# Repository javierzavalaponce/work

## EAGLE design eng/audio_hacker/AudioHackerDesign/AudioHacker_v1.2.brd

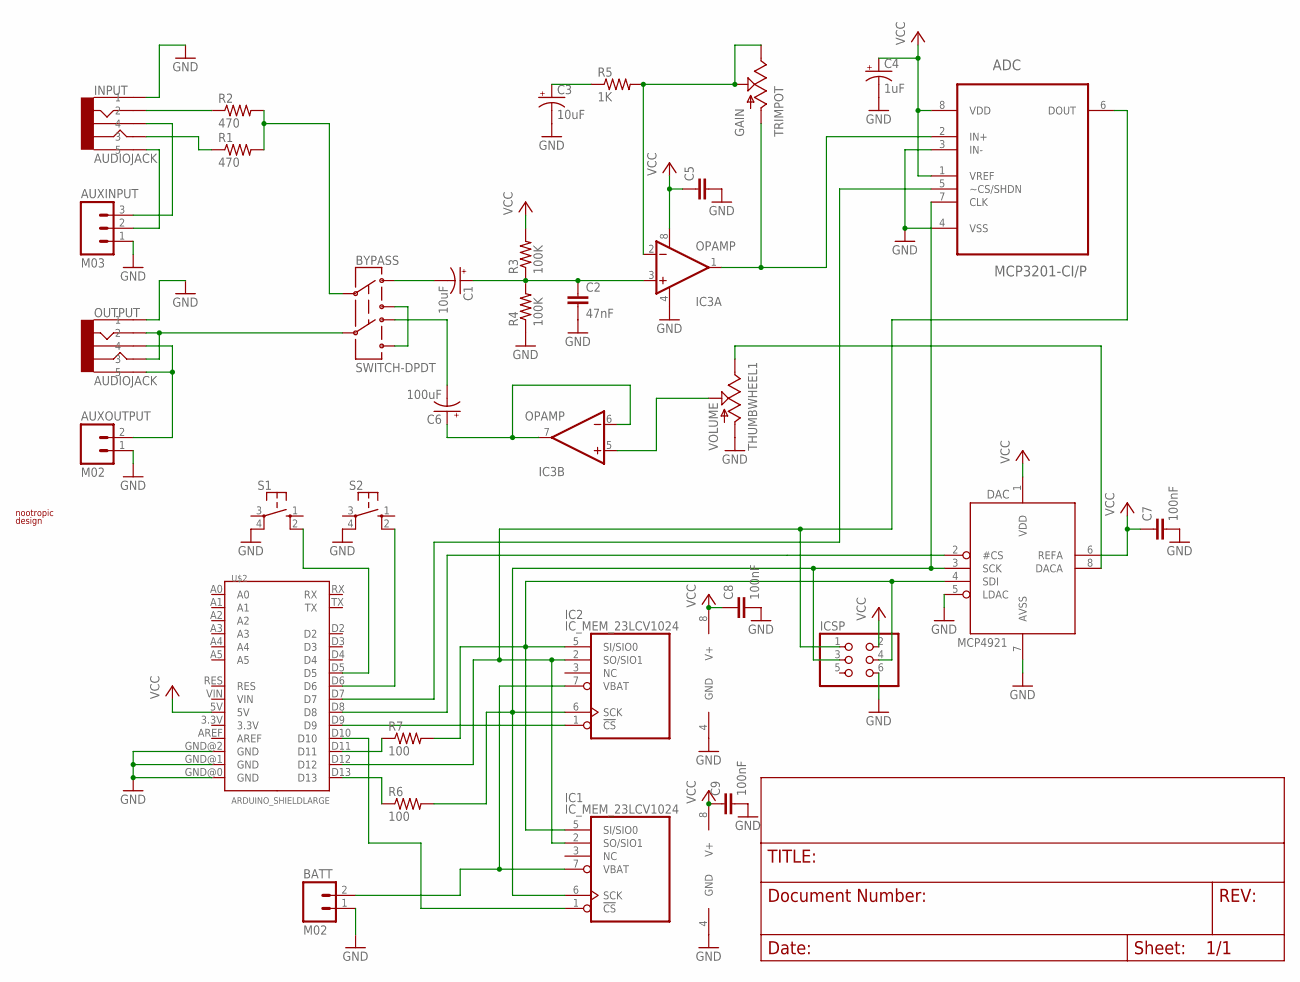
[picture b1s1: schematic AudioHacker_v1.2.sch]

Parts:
ADC: MCP3201-CI/P; DIL08
AUXINPUT: M03; 1X03
AUXOUTPUT: M02; 1X02
BATT: M02; 1X02
BYPASS: SWITCH-DPDT; OS
C1, C3: 10uF; E2.5-5
C2: 47nF; CAP-CERAMIC
C4: 1uF; E2.5-5
C5: CAPSMALL; CAP-CERAMIC-SMALL
C6: 100uF; E2.5-6
C7, C8, C9: 100nF; CAP-CERAMIC-SMALL
DAC: MCP4921; DIL08
GAIN: TRIMPOT; TRIM_POT
IC1, IC2: IC_MEM_23LCV1024; DIL08
IC3: OPAMP; DIL08
ICSP: PINHD-2X3; 2X03
INPUT: AUDIOJACK
OUTPUT: AUDIOJACK
R1, R2: 470; 0207/10
R3, R4: 100K; 0207/10
R5: 1K; 0207/10
R6, R7: 100; 0207/10
S1, S2: SWITCH-TACTSWITCH-TACT-B; SWITCH-TACT-B
U$2: ARDUINO_SHIELDLARGE; DUEMILANOVE_SHIELD_LARGE
U$3: LOGO; LOGO_SMALL
VOLUME: THUMBWHEEL1

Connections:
AMP_OUT: C6.+, IC3.6 (-IN), IC3.7 (OUT)
DAC_OUT: DAC.8 (DACA), VOLUME.P$3 (3)
DAC_OUT2: IC3.5 (+IN), VOLUME.P$2 (2)
GND: ADC.3 (IN-), ADC.4 (VSS), AUXINPUT.1 (2), AUXOUTPUT.1, BATT.1, C2.2, C3.-, C4.-, C5.2, C7.2, C8.2, C9.2, DAC.5 (LDAC), DAC.7 (AVSS), IC1.4 (GND), IC2.4 (GND), IC3.4 (V-), ICSP.6, INPUT.1, OUTPUT.1, R4.1, S1.4 (P1), S2.4 (P1), U$2.GND@0 (GND), U$2.GND@1 (GND), U$2.GND@2 (GND), VOLUME.P$1 (1)
INPUT: BYPASS.2, R1.2, R2.2
MISO: ADC.6 (DOUT), IC1.2 (SO/SIO1), IC2.2 (SO/SIO1), ICSP.1, U$2.D12
MOSI: DAC.4 (SDI), IC1.5 (SI/SIO0), IC2.5 (SI/SIO0), ICSP.4, R7.2
MOSIPIN: R7.1, U$2.D11
unnamed: AUXINPUT.3 (4), INPUT.4
unnamed: AUXINPUT.2 (3), INPUT.5
unnamed: AUXOUTPUT.2, OUTPUT.4, OUTPUT.5
unnamed: BYPASS.3, BYPASS.6
unnamed: INPUT.2, R2.1
unnamed: INPUT.3, R1.1
unnamed: GAIN.2, GAIN.3, IC3.2 (-IN), R5.2
unnamed: ADC.2 (IN+), GAIN.1, IC3.1 (OUT)
unnamed: C3.+, R5.1
unnamed: BYPASS.1, C1.-
unnamed: C1.+, C2.1, IC3.3 (+IN), R3.1, R4.2
unnamed: BYPASS.4, C6.-
unnamed: R6.1, U$2.D13
unnamed: ADC.5 (~CS/SHDN), U$2.D7
unnamed: DAC.2 (#CS), U$2.D8
unnamed: S2.2 (S1), U$2.D6
unnamed: IC1.1 (!CS), U$2.D10
unnamed: IC2.1 (!CS), U$2.D9
unnamed: S1.2 (S1), U$2.D5
OUTPUT: BYPASS.5, OUTPUT.2, OUTPUT.3
SCK: ADC.7 (CLK), DAC.3 (SCK), IC1.6 (SCK), IC2.6 (SCK), ICSP.3, R6.2
VBAT: BATT.2, IC1.7 (VBAT), IC2.7 (VBAT)
VCC: ADC.1 (VREF), ADC.8 (VDD), C4.+, C5.1, C7.1, C8.1, C9.1, DAC.1 (VDD), DAC.6 (REFA), IC1.8 (V+), IC2.8 (V+), IC3.8 (V+), ICSP.2, R3.2, U$2.5V

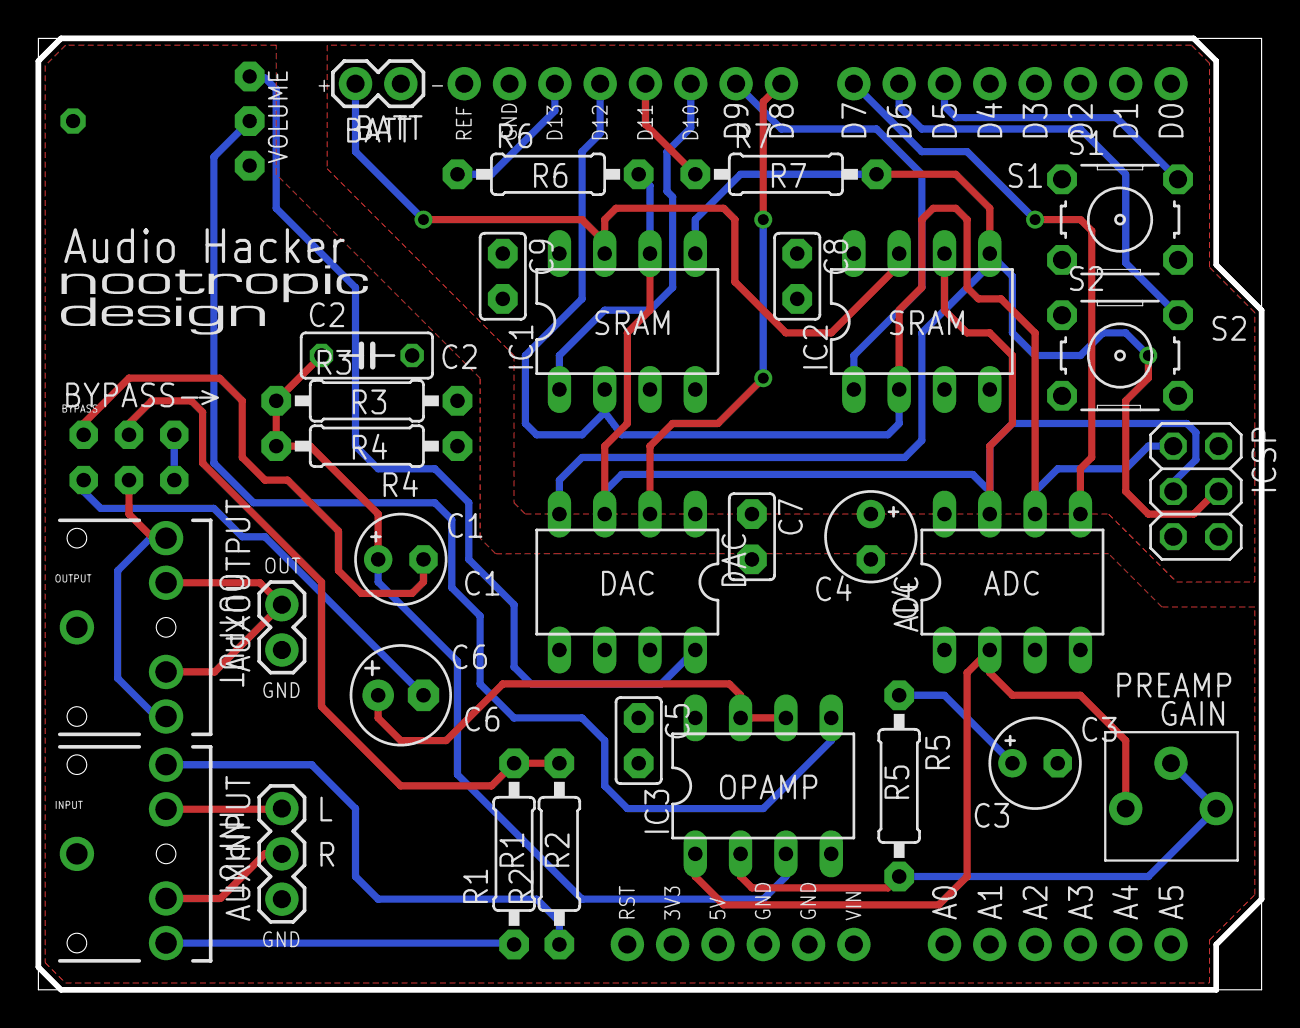
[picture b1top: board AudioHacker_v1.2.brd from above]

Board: 2 copper layers, 68.6 x 53.3 mm, 34 parts (0 on the bottom side), 31 nets.

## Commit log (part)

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2026-03-04 ignore virtual envs de python
2026-03-04 del folder
2026-03-04 add folder to git
2026-03-04 add folders
2026-03-04 fix relative paths
2026-03-04 fix relative path
2026-03-04 fix paths
2026-03-04 more fixes path realed (relative)
2026-03-04 gitignore all build folders
2026-03-04 fix template
2026-03-04 start install esp32
2026-03-06 keep track
2026-03-09 emulacion de RC sobre arduino
2026-03-09 experimentando RC como filtro pBajas
2026-03-11 resp en freq de RC
2026-03-11 principio de estudio - fourier
2026-03-11 funcion transferencia y bode con python
2026-03-14 Audio hacker board data
2026-03-14 start audio prj
2026-03-14 audio hacker schematic
2026-03-14 audio en pc ur22
2026-03-14 start audio prj ur22
2026-03-14 delay con feedback
2026-03-14 respalda comando
2026-03-14 julia audio first try ok
2026-03-14 audio smple
2026-03-15 bakp notsas
2026-03-16 capture a0
2026-03-16 capture audio 100 Hz
2026-03-16 add display 16x2wq
2026-03-16 todo listwq
2026-03-17 chirp filtrada por RC julia-arduino
2026-03-20 start plan
2026-03-20 aqui voy
2026-03-21 planeacion[F
2026-03-21 primer version de dsp
2026-03-21 trabajando planeacion
2026-03-21 librosa ejemplo, sin testeo
2026-03-21 backlog items added
2026-03-26 start study: valores propios
2026-03-29 first mixer
2026-03-29 it works - new baseline
2026-03-30 add Fx echo delay
2026-03-30 kb control basic
2026-03-30 initial test ok
2026-03-30 testing adoro chavela
2026-03-30 delay con filtro
2026-04-02 playing with mi minidaw
2026-04-07 programacion funcional
2026-04-07 integrador
2026-04-07 oscilador colpits en ngspice
2026-04-08 add notas de ideas y plan de trabajo doctoral - ideas sueltas
2026-04-14 start reporte thinking in systems
2026-04-14 gradiente en julia
2026-04-17 ejercicio de gradiente en julia
2026-04-18 SICP traduccion
2026-04-19 reporte02 de md a latex con pandoc
2026-04-19 reporte 02 mejoras
2026-04-19 reporte 02 - avances
2026-04-19 casi listo reporte 2
2026-04-19 reporte 002- in progress
2026-04-19 marca donde voy -
2026-04-19 reporte 02 latest
2026-04-19 algunos ejemplos de racket - lisp
2026-04-20 reporte 003
2026-04-21 genera reporte3
    de preferencia , remover la parte
    de bolton de que no lo he conseuido
    Wq:
2026-04-21 add Soporte a Referencias
2026-04-21 listo reporte 3 con biblio
2026-04-21 start Reporte 4
2026-04-21 NUEVO rport 3 - el bueno
2026-04-23 bolton 1er approx
2026-04-24 organizando ideas
2026-04-24 org ..
2026-04-25 nothing special
2026-04-25 start - primer test dc motor 12 V- ok
2026-04-26 test encoder mag
2026-04-26 testing encoder mag y driver - ok , pos mal
2026-04-27 avances
2026-04-28 cambio de png a pdf diagrama ctrl
2026-04-29 solucion num
2026-04-29 add explicacion de quiver
2026-04-29 reporte 4
2026-04-30 add mising pdf files
2026-04-30 aprendiendo root locus
2026-05-02 reporte 5 - init
2026-05-02 reporte 005 - Ready
2026-05-03 rc julia - reporte 005
2026-05-05 missing pdf added
2026-05-05 new cambios
2026-05-05 reporte 006
2026-05-06 criterio de routh hwitz
2026-05-09 -ok , avance menor - completar RC sist 1er orden
2026-05-09 comentarios RC
2026-05-09 mejoras reporte RC
2026-05-09 reorganizando
2026-05-09 reorganizacion 2
2026-05-09 usa .yaml para cfg, genpdf y zathura cfg
2026-05-10 avances fin de semana
2026-05-10 testin lap ok
2026-05-10 install aid zathura
2026-05-10 keep track of zathura settings
2026-05-10 reglas rlocus
2026-05-10 mas avances rlocus reglas
2026-05-10 mas avances: reglas rlocus
2026-05-10 reporte 7
2026-05-10 sunday
2026-05-11 testin encoder 00
2026-05-11 mark
2026-05-11 pausa reflexiona - studio
2026-05-11 arduino cfg
2026-05-12 minor improvement
2026-05-12 inicio PI
2026-05-13 cap 3 bolton - done
2026-05-15 Figure -> FigurA cfg header.tex
2026-05-15 avances del PI
2026-05-15 renaming strategy
2026-05-15 polos y ceros
2026-05-15 avances en tema de polos y ceros
2026-05-15 ceros y polos
2026-05-15 graficas dfe polos
2026-05-16 ceros y polos redondeando
2026-05-16 midiendo rpm vw wiper
2026-05-17 playin
2026-05-17 mejoras
2026-05-17 modo
2026-05-18 reporte 008
2026-05-19 guion largo contra guion corto
2026-05-19 pdflatex + babel automático de pandoc
2026-05-20 avance
2026-05-21 avancescistos
2026-05-22 diaatriba
2026-05-24 reporte 9
2026-05-24 avances ejemplo de pi
2026-05-26 intro a redes neuronales
2026-05-26 correccion pi ejercicio de examen
2026-05-28 diagrama de apoyo
2026-05-28 espacio y estados 1a version
2026-05-28 espacio y edos contin
2026-05-29 integrator
2026-05-30 reportee 10
2026-05-30 precontrl mejoras
2026-05-30 mejoras explicacion tanque
2026-05-31 primer diagrama con integrador simple
2026-05-31 mejoras reporte10 - solicitud de revision
2026-06-01 convlucion estudio
2026-06-02 octave de ss a ft
2026-06-02 avances espacio edos ejercicio
2026-06-02 dia diagrama espacio edos
2026-06-03 completo ejercicio espacio y edos, octave
2026-06-03 mejoras menores
2026-06-08 observabilidad
2026-06-09 fzf mejorando navegacion en vim
2026-06-10 mejoras a vimrc
2026-06-11 respaldo del bashrc de lap con xclip
2026-06-12 carpeta snip para snipets latex
2026-06-12 youtube channel screenshot modelado data based
2026-06-13 start folder con snippets
2026-06-13 ready pra review
2026-06-13 del cmds.h
2026-06-13 add cmd to clean latex compil
2026-06-13 dismissing cap8 sist din julia
2026-06-13 separa reporte de sist dinamicos en julia
2026-06-13 separa reporte de clases de Dr. Basilio
2026-06-13 separa julia pdf
2026-06-13 separa reporte profesor basilio
2026-06-13 fixing all
2026-06-13 start documento de clases de Dr. Domingo
2026-06-13 rename folders
2026-06-13 mejoras reporte sis dinamic julia
2026-06-14 practicando xppaut
2026-06-15 minor fix
2026-06-16 avances reporte clases Dr. Domingp
2026-06-16 synch
2026-06-16 kata de ploteo para practicar
2026-06-16 minor improvements
2026-06-16 updates clases Dr. Basilio
2026-06-18 katas practice
2026-06-18 reorganizacion de carpetas
2026-06-18 resuelve ec diferencial xppaut -> gnuplot ejemplo
2026-06-19 proyecto idea de propuesta
2026-06-22 avances notas Dr Domingo
2026-06-23 notas extras proyecto 4
2026-06-24 propuesta - ensayo 4
2026-06-25 paquete octave fuzzy
2026-06-25 avances gaussiana
2026-06-25 gausiana tested ok - uso de ipython 1rst trial
2026-06-25 docustring faltan alias y return to func
2026-06-26 added sigmoide
2026-06-26 first draft prj04
2026-06-26 start 05 markov docu add to sis din julia
2026-06-26 modelo openscad - trial
2026-06-27 tag furuta.scad
2026-06-28 furuta3
2026-06-29 avances notas ctrl difuso
2026-06-30 ctrl difuso
